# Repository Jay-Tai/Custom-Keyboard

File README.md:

# The Megaboard

The megaboard is a custom 60% keyboard that has 65 keys in total, and has many unique functions that truly make this project a one-of-the-kind.

I built this project to participate in [Hack Club's Stardance](http://stardance.hackclub.com/), and fell in love with the development of keyboards very quickly after I started!
## Features
- Amazing 3D printed case
- 0.91" OLED for animations, startup, and for other tools, such as WPM, and Caps Lock
- SK6812 Mini-E LEDs for under-key glow
- EC11 Rotary Encoder to control volume, scroll through pages, or press down to mute/unmute your zoom meeting
- 65 Akko V3 Cream Yellow Pro keys for your satisfying typing experience needs :D (Cheap and sounds like heaven)
- Topographic look all-around (Part of the PCB is exposed)
w
## CAD Model
All the parts of this project fit together using 2 m2.5 screws.
It has 2 seperate printed pirces, one to be the main base, and the other one to cover the electronics.

Made in OnShape.

## PCB
Here's my PCB! it was made in KiCad. Some footprints and schematics were from marbastlib. I made the silkscreen in Adobe Illustrator.
#### Here is my schematic

#### Here is my PCB

The PCB has 2 copper layers, and all the parts that are needed are part of the PCB design. I think in retrospect, I should have moved the arrow keys to the bottom of the PCB, instead of it being at the top.

## Firmware overview
This hackpad's firmware has been designed in [QMK](https://qmk.fm/). It is a powerful, yet simple way to design keyboards that have a lot of useful functions!
- The rotary encoder controls the volume of the computer, and when you hold FN, you can scroll. When you press the encoder, it will mute/unmute your zoom call.
- The 65 keys all perform different functions that can be adjusted by simply changing it's function in keymap.c.
- The OLED starts off with a startup animation, and then after, it turns into a cat! Specifically, the Bongocat!! <b>Credits to [nwii's bongocat](https://github.com/nwii/oledbongocat) for the source code!</b>
- All keys have SK6812 Mini-E LEDs beneath them and when you press a key, its LED will light up in a reactive typing way. Take a look [here](https://youtu.be/7f3usatOIKM?t=229)!

I might add more in the future, however, that's it for now!

## BOM
Here is everything that you will need to make the megaboard:
Click [here](https://docs.google.com/spreadsheets/d/1aInlIyzgglzUiH9fcOGwBJfbiqagTssbSa5kihXWXrg/edit?usp=sharing)

## Thank you!
Thank you for taking a look! This was a huge undertaking to make this entire project, and I spent over 50 hours to make this!

Especially, thank you to [Hack Club](https://hackclub.com/) for inspiring me to make this project, and thank you to [nwii's bongocat](https://github.com/nwii/oledbongocat) animation for part of the OLED!

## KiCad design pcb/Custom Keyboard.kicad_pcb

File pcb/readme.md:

# PCB Files
The following files are all KiCad files. Download all the files and put them in a folder, and put it in KiCad to edit the PCB!

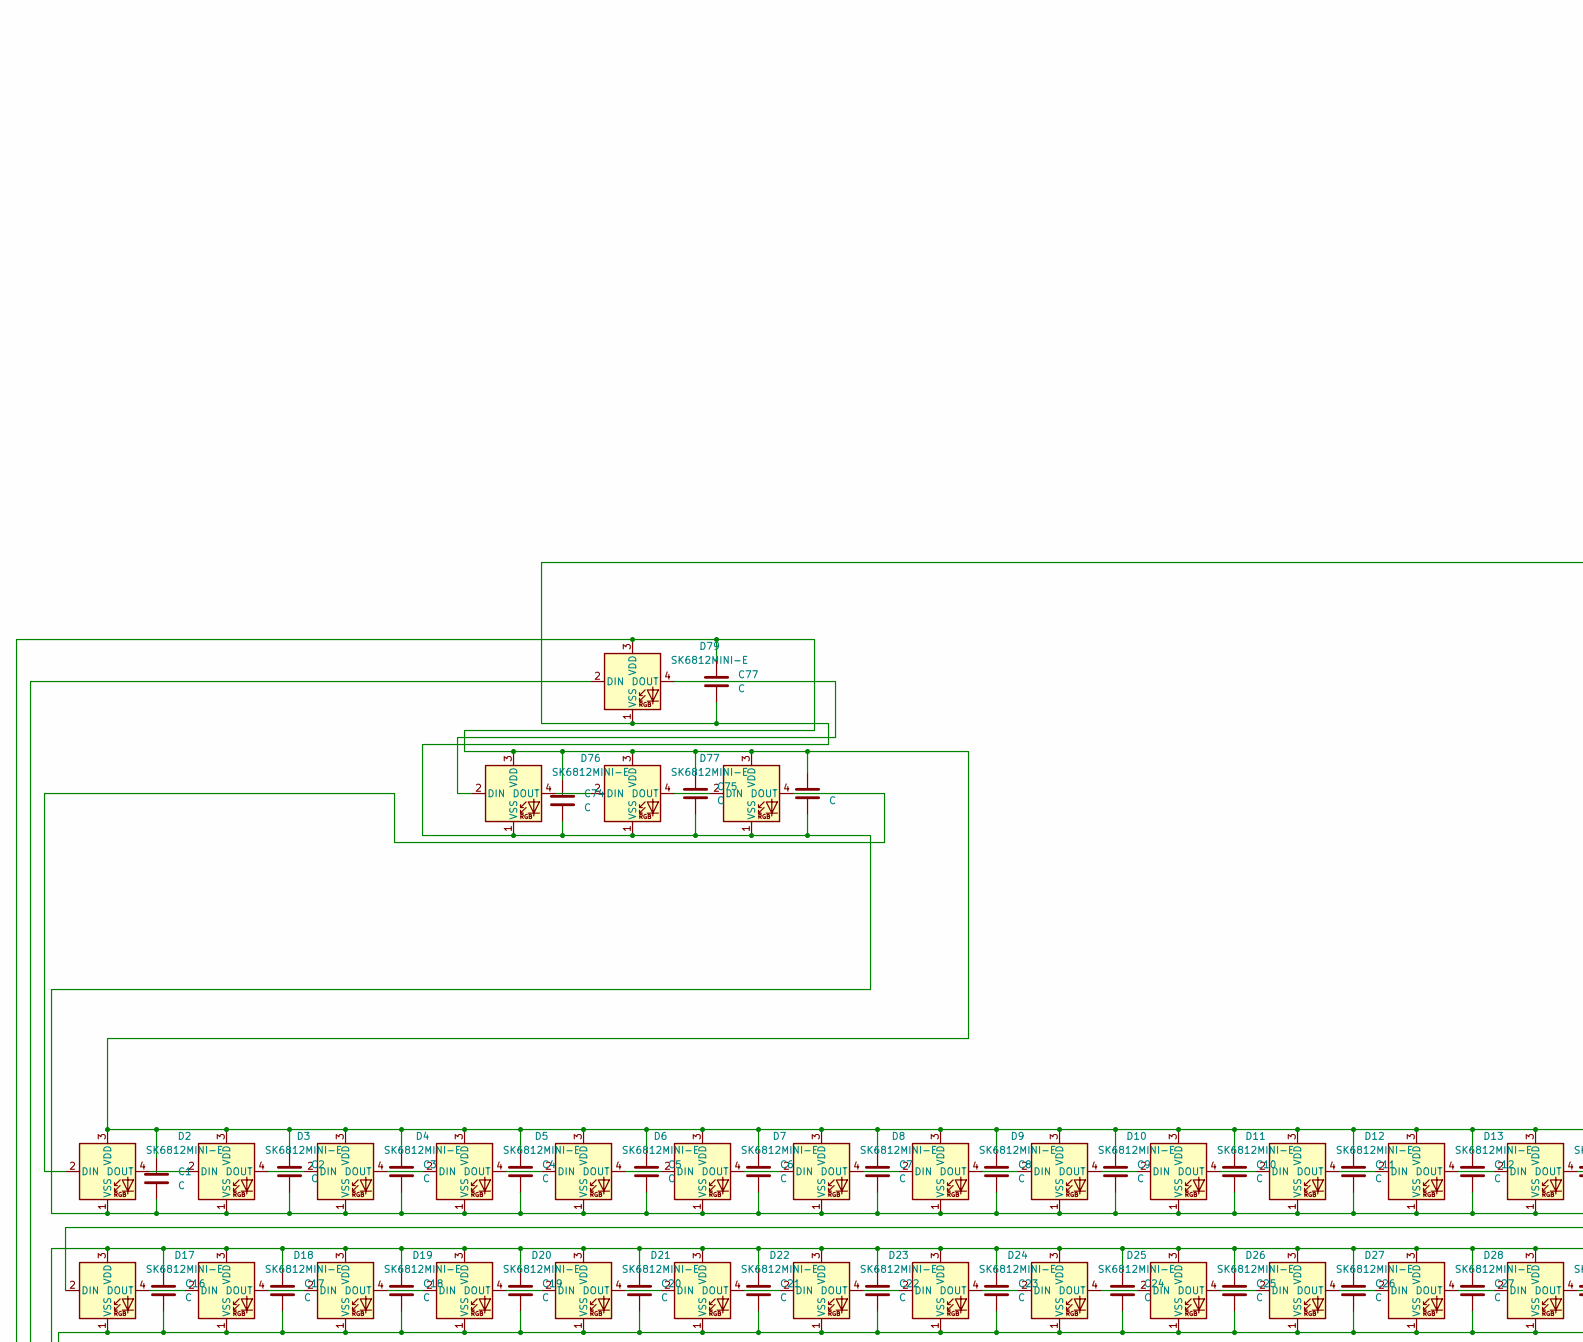
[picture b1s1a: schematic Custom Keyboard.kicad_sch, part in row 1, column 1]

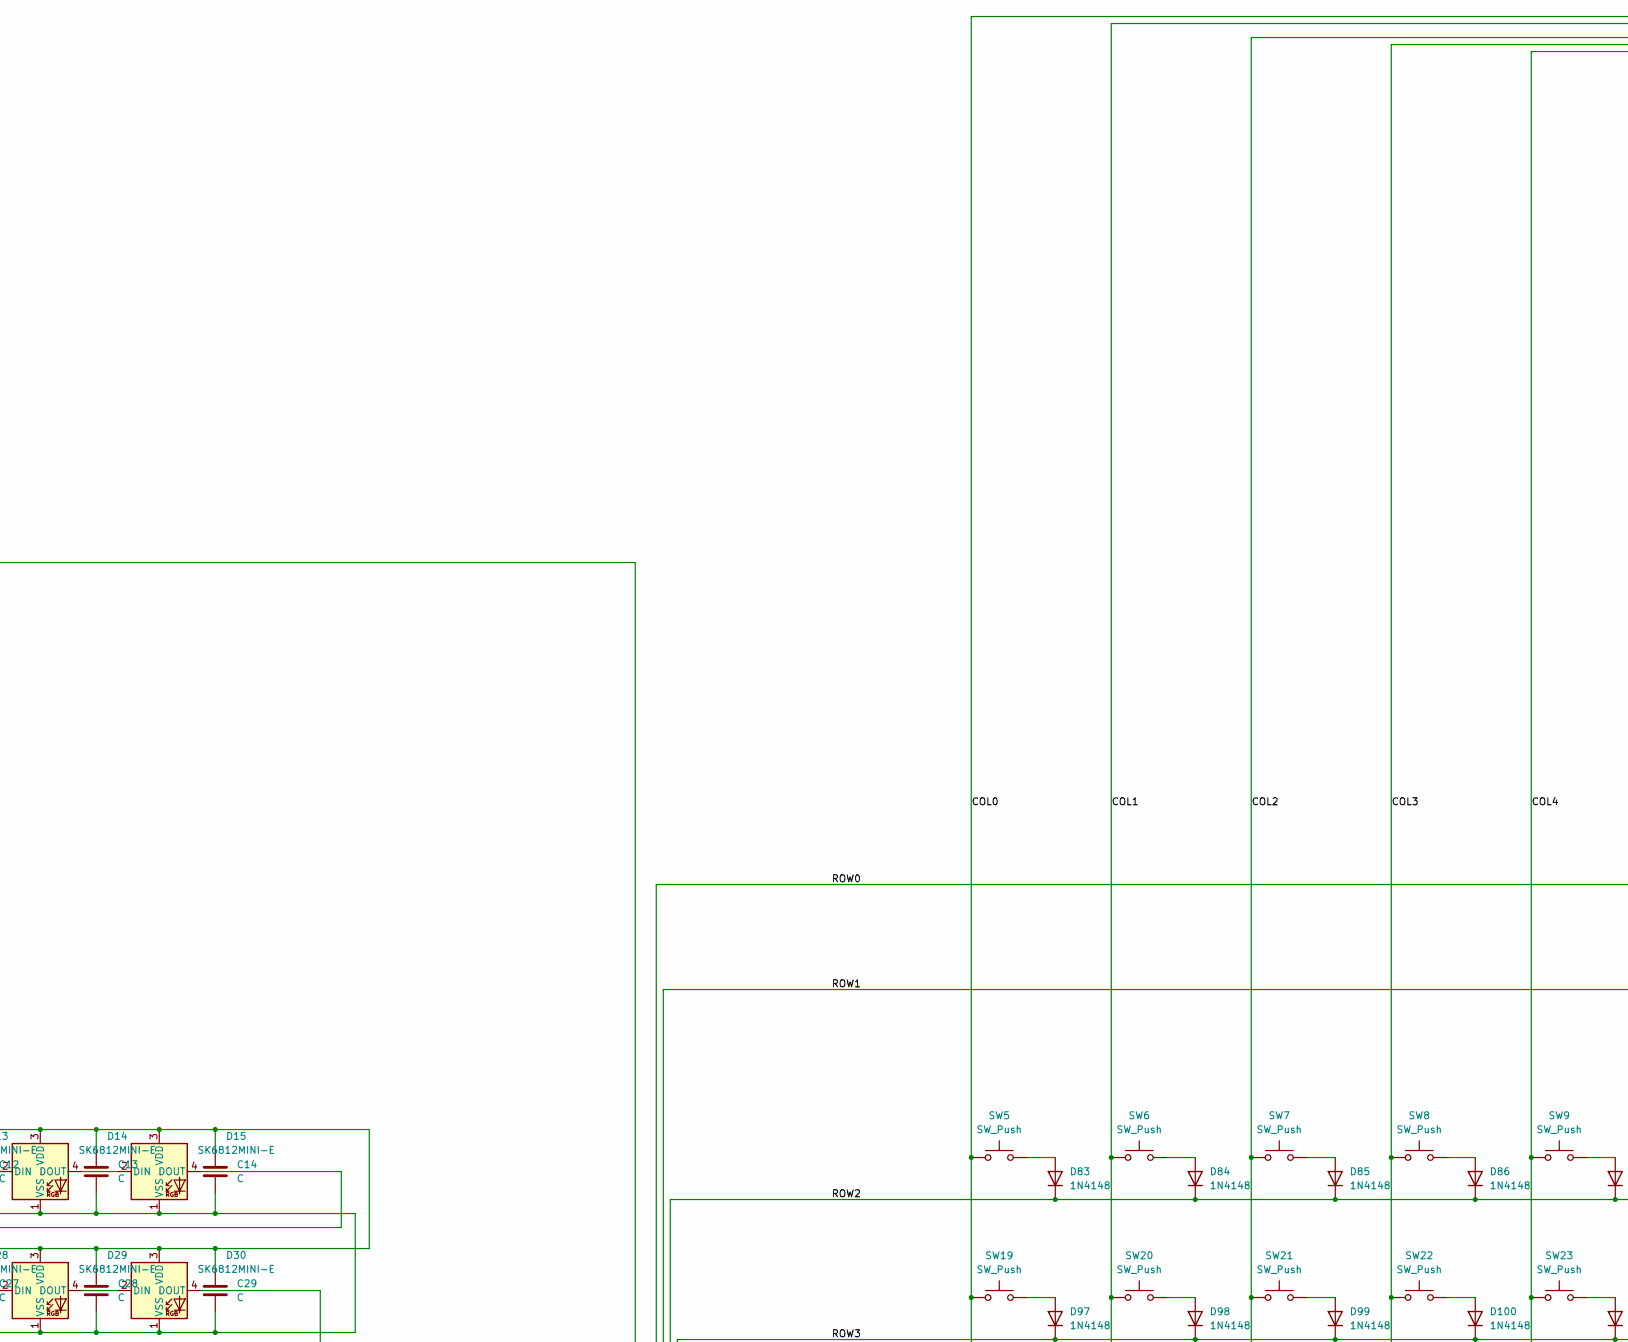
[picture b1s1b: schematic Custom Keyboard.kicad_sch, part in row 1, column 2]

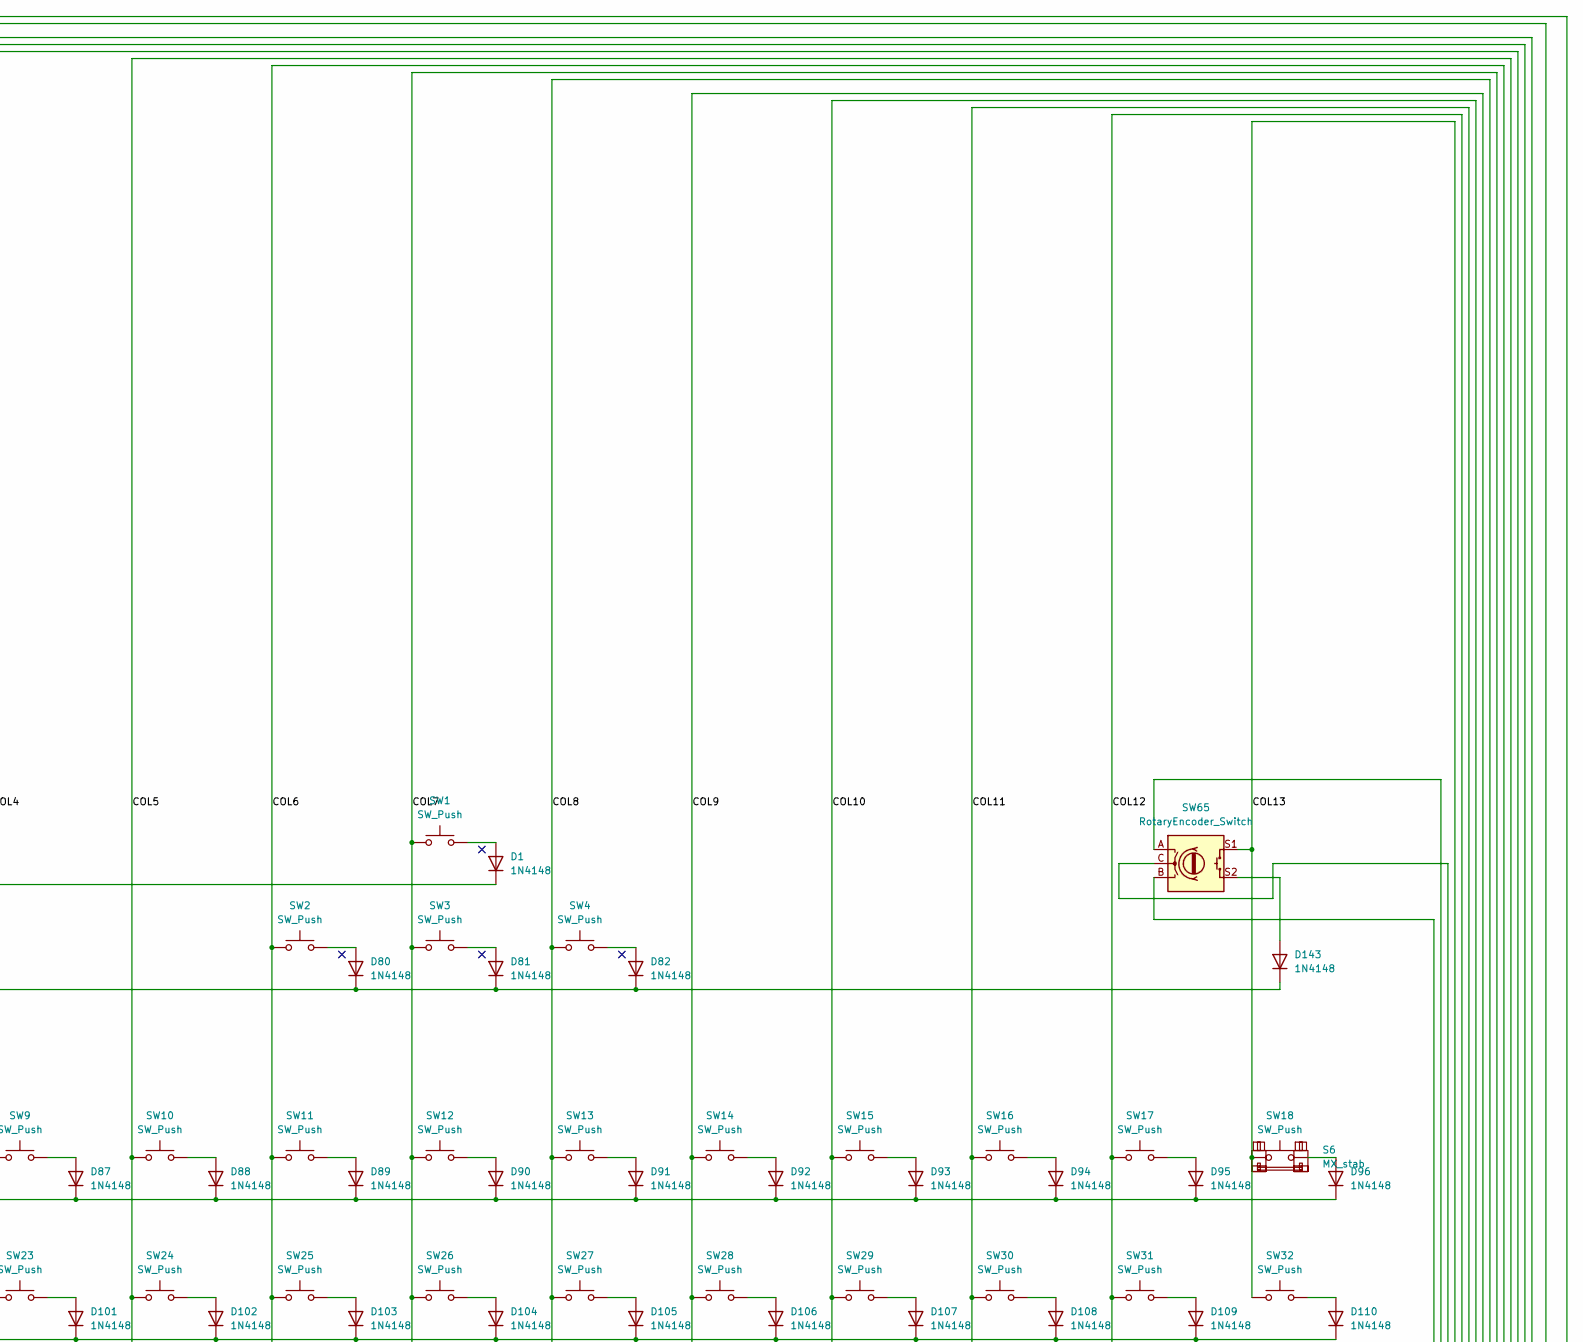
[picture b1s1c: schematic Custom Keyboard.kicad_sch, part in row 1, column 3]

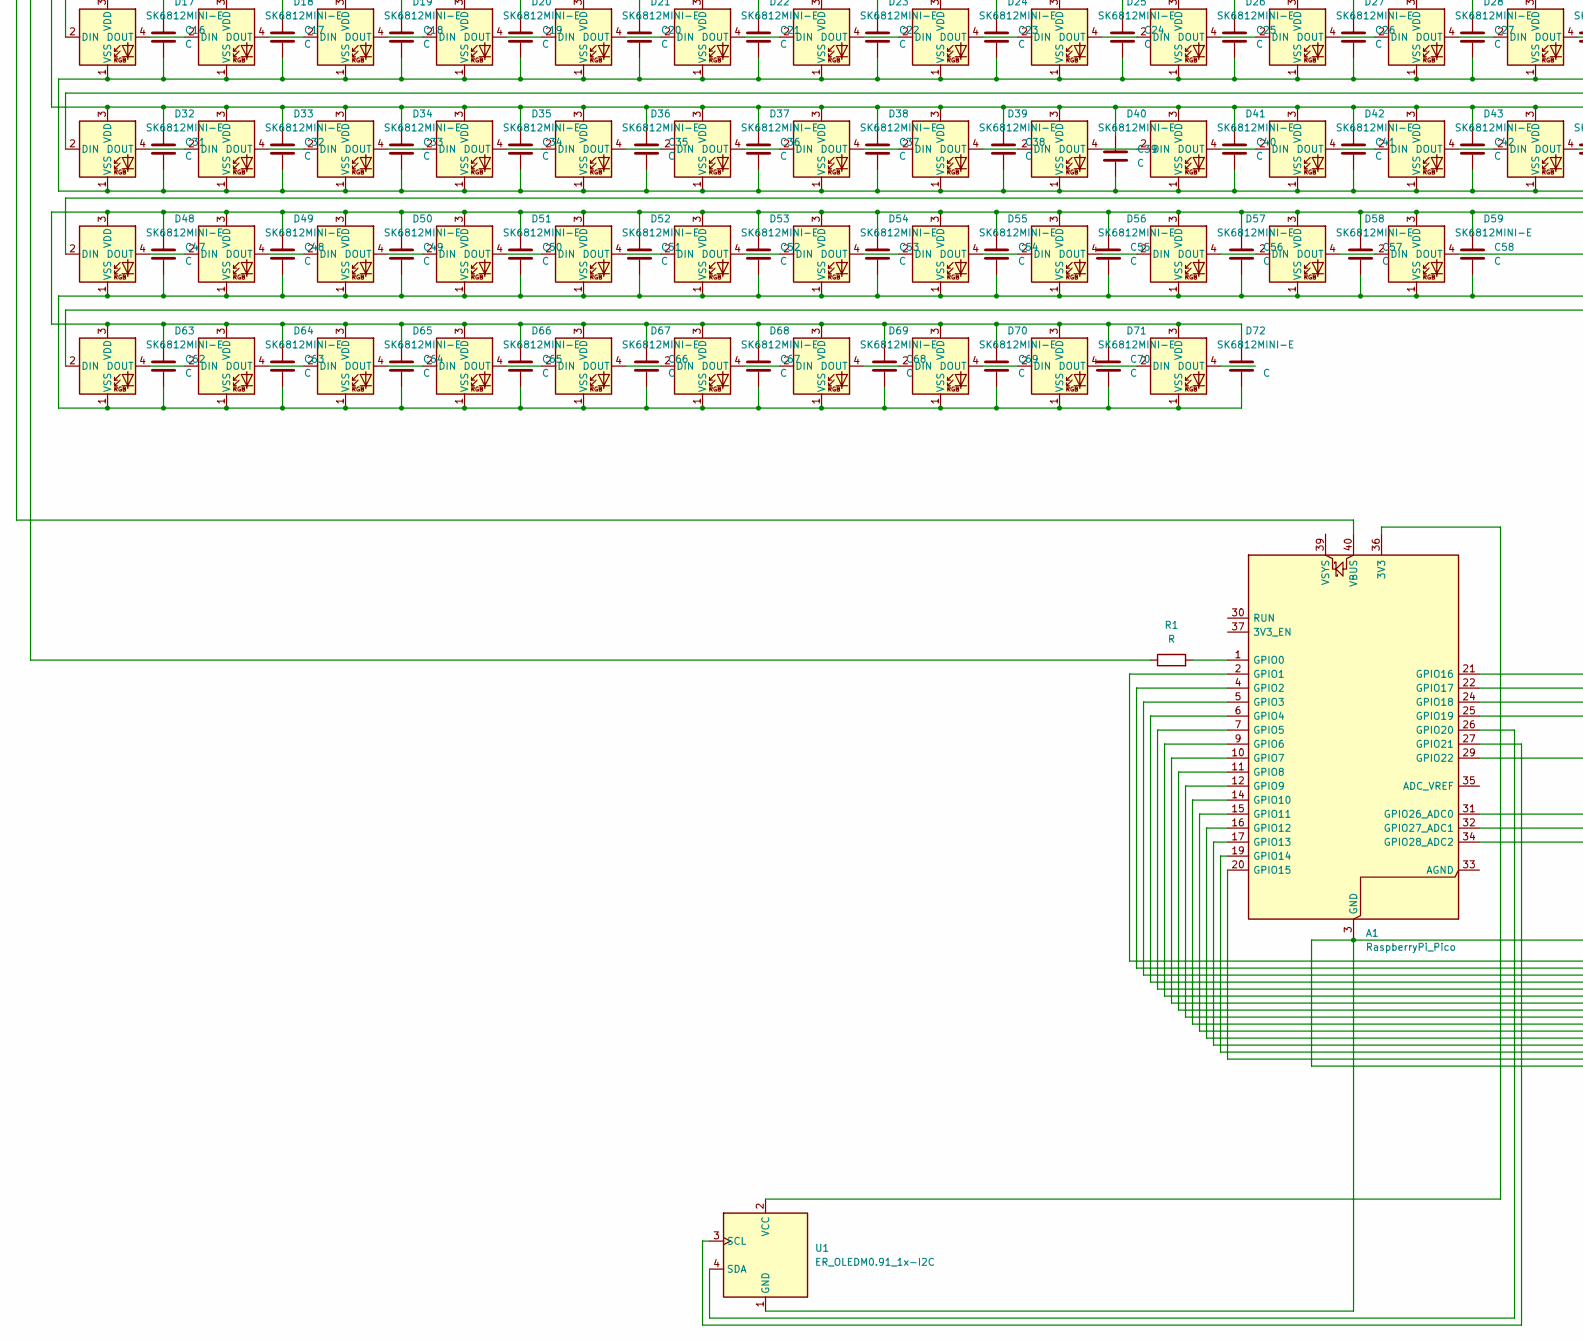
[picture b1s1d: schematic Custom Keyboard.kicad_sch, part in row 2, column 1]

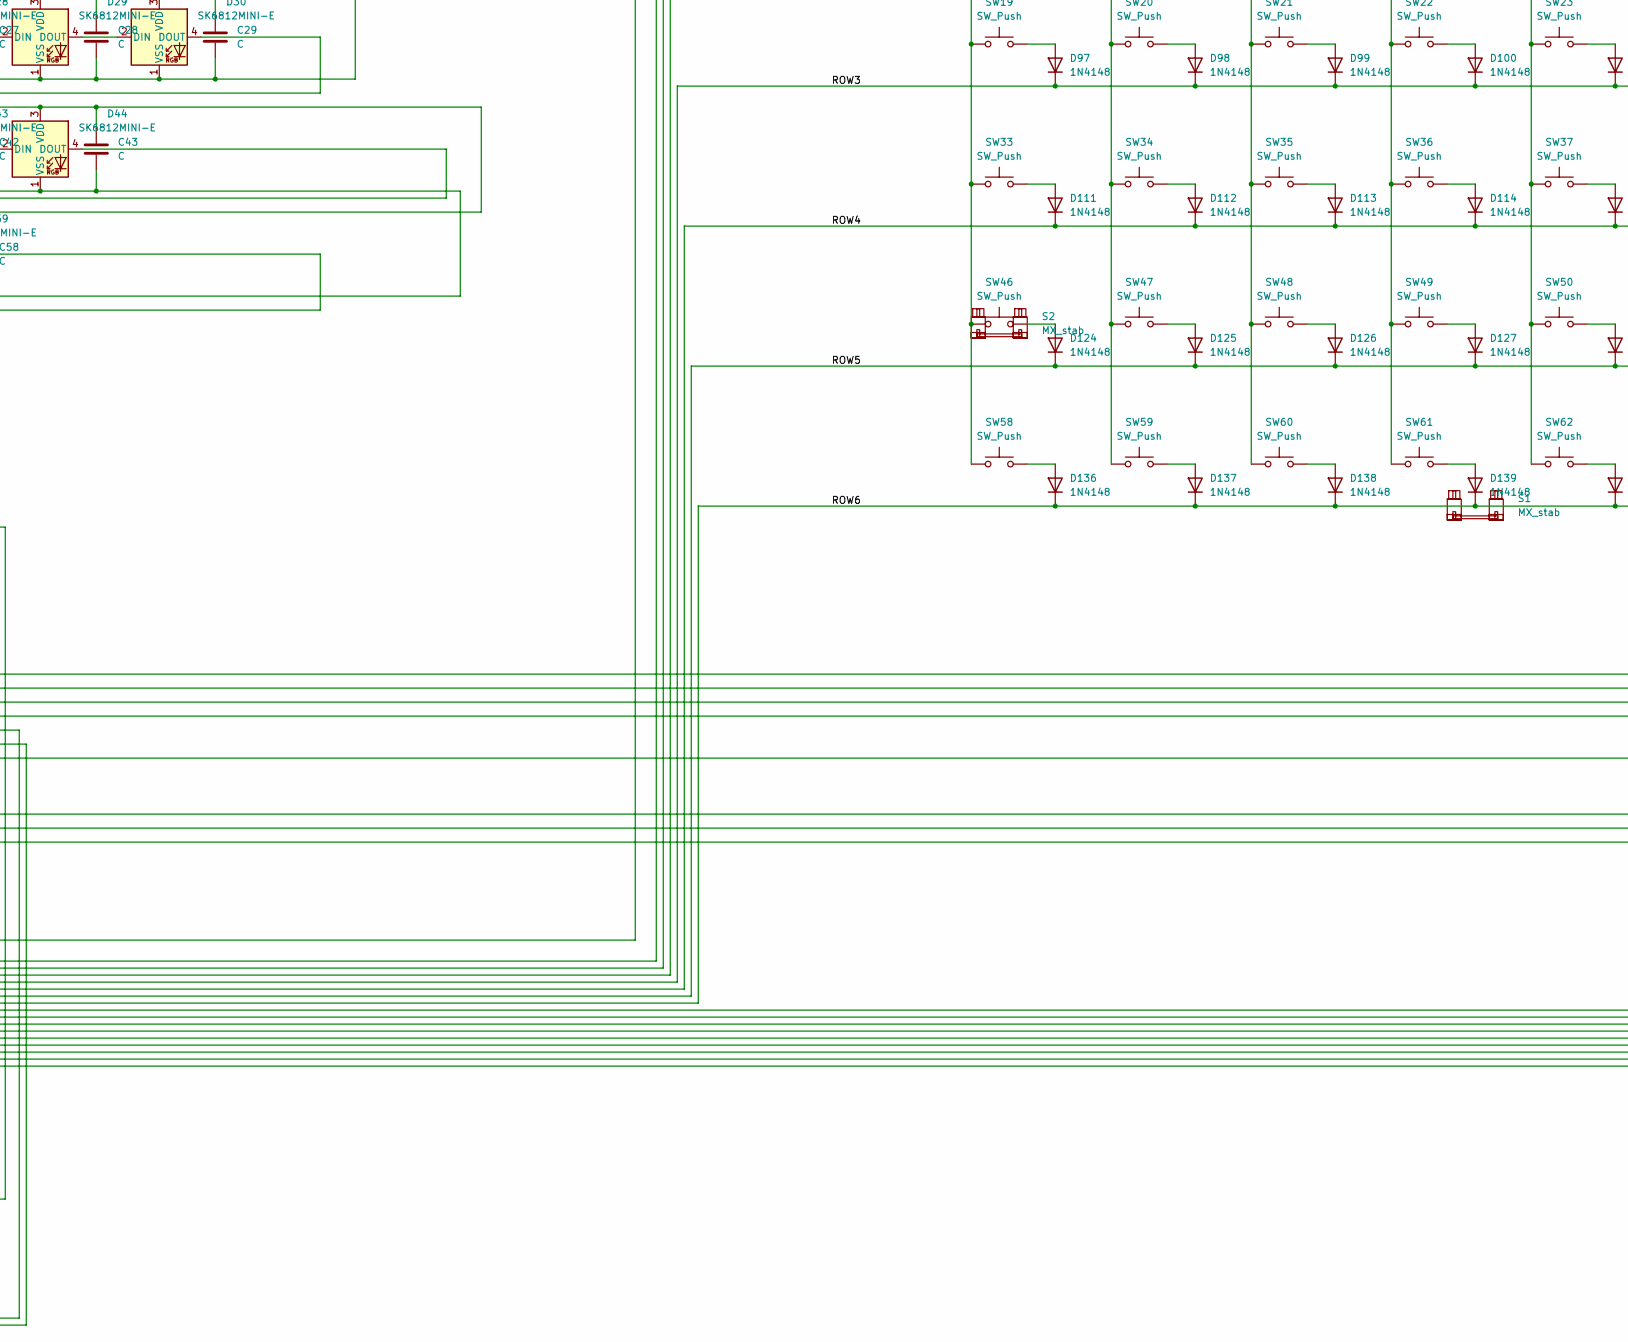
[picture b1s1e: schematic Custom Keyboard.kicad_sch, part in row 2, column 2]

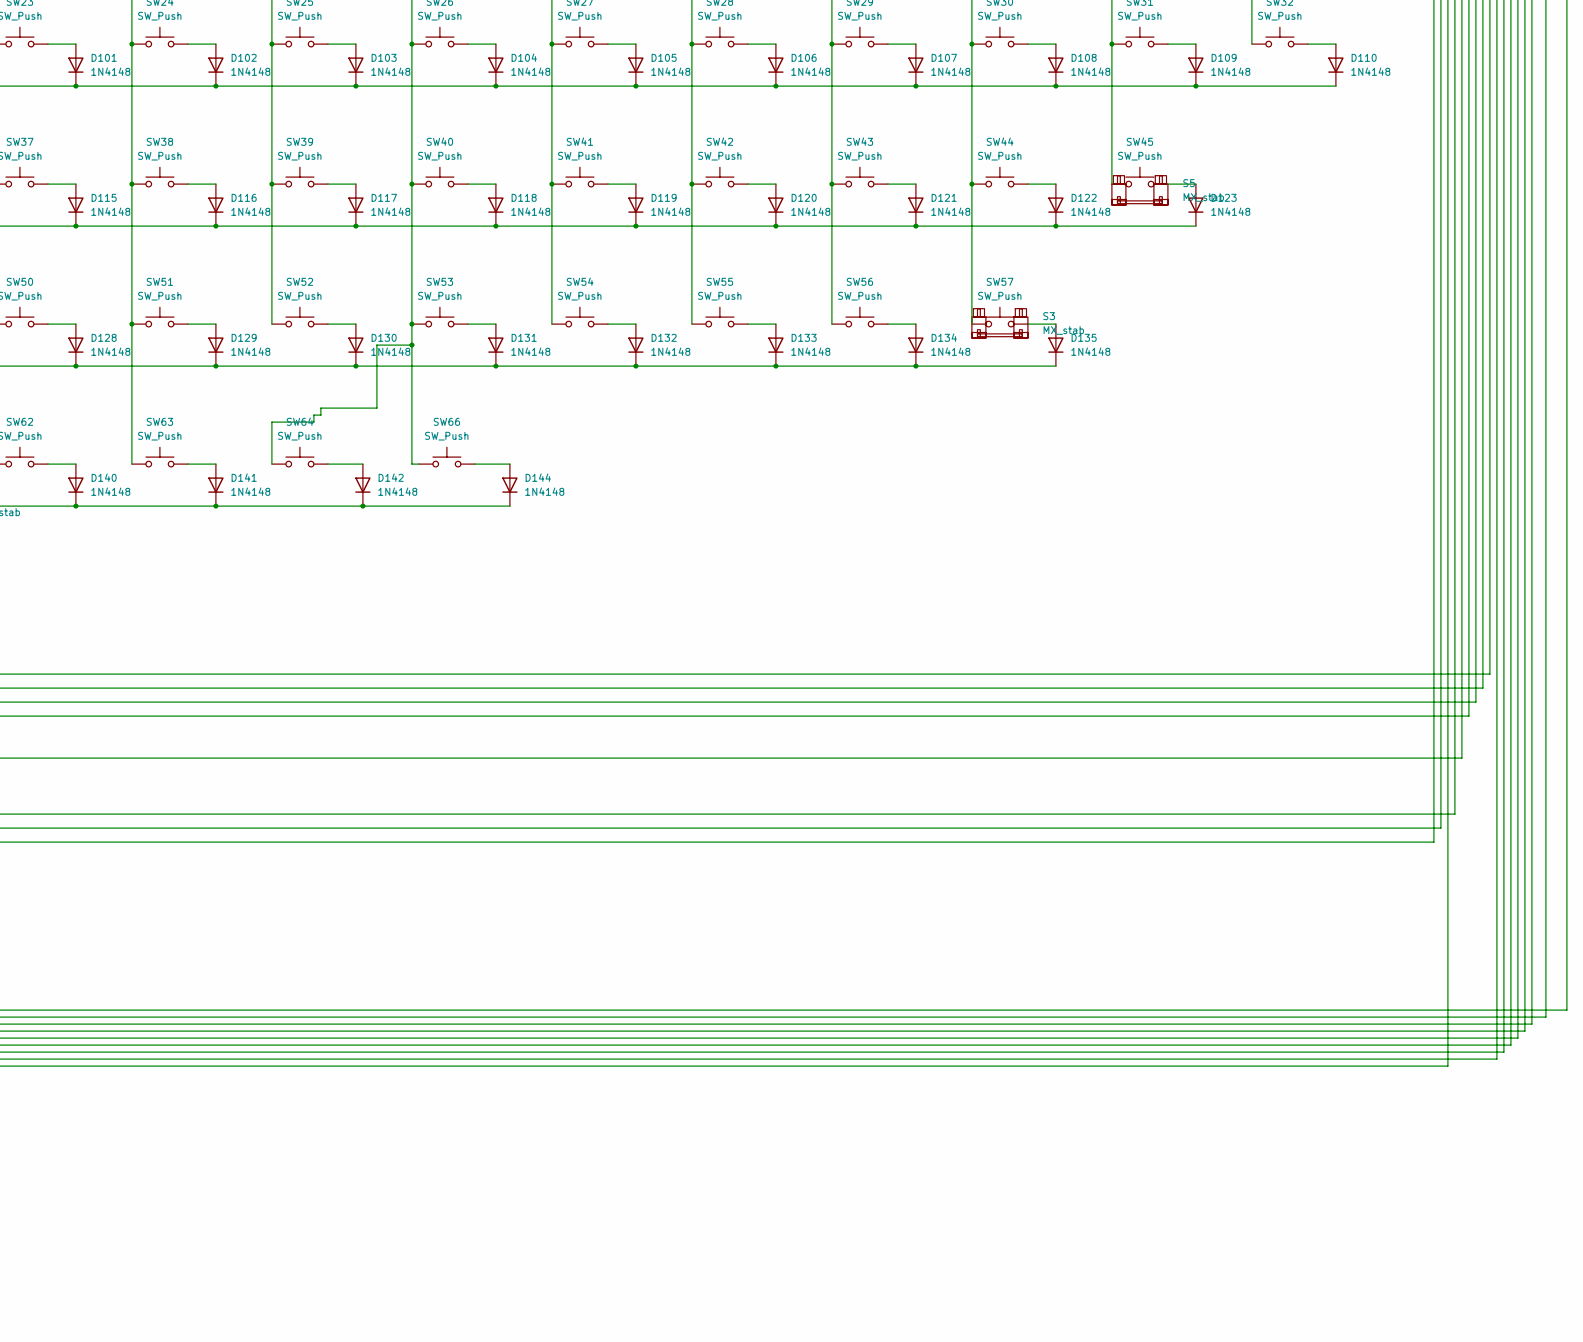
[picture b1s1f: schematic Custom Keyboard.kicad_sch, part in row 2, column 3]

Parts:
A1: RaspberryPi_Pico; RaspberryPi_Pico_Common_THT
C1, C2, C3, C4, C5, C6, C7, C8, C9, C10, C11, C12, C13, C14, C16, C17, C18, C19, C20, C21, C22, C23, C24, C25, C26, C27, C28, C29, C31, C32, C33, C34, C35, C36, C37, C38, C39, C40, C41, C42, C43, C47, C48, C49, C50, C51, C52, C53, C54, C55, C56, C57, C58, C62, C63, C64, C65, C66, C67, C68, C69, C70, C71, C74, C75, C76, C77: C; C_0603_1608Metric_Pad1.08x0.95mm_HandSolder
D1, D80, D81, D82, D83, D84, D85, D86, D87, D88, D89, D90, D91, D92, D93, D94, D95, D96, D97, D98, D99, D100, D101, D102, D103, D104, D105, D106, D107, D108, D109, D110, D111, D112, D113, D114, D115, D116, D117, D118, D119, D120, D121, D122, D123, D124, D125, D126, D127, D128, D129, D130, D131, D132, D133, D134, D135, D136, D137, D138, D139, D140, D141, D142, D143, D144: 1N4148; D_DO-35_SOD27_P7.62mm_Horizontal
D2, D3, D4, D5, D6, D7, D8, D9, D10, D11, D12, D13, D14, D15, D17, D18, D19, D20, D21, D22, D23, D24, D25, D26, D27, D28, D29, D30, D32, D33, D34, D35, D36, D37, D38, D39, D40, D41, D42, D43, D44, D48, D49, D50, D51, D52, D53, D54, D55, D56, D57, D58, D59, D63, D64, D65, D66, D67, D68, D69, D70, D71, D72, D76, D77, D78, D79: SK6812MINI-E; LED_SK6812MINI-E_3.2x2.8mm_P1.5mm_ReverseMount
R1: R; R_0805_2012Metric
S1: MX_stab; STAB_MX_P_6.25u
S2, S5: MX_stab; STAB_MX_2.25u
S3: MX_stab; STAB_MX_P_2.75u
S6: MX_stab; STAB_MX_2u
SW1, SW2, SW3, SW4, SW5, SW6, SW7, SW8, SW9, SW10, SW11, SW12, SW13, SW14, SW15, SW16, SW17, SW18, SW19, SW20, SW21, SW22, SW23, SW24, SW25, SW26, SW27, SW28, SW29, SW30, SW31, SW32, SW33, SW34, SW35, SW36, SW37, SW38, SW39, SW40, SW41, SW42, SW43, SW44, SW45, SW46, SW47, SW48, SW49, SW50, SW51, SW52, SW53, SW54, SW55, SW56, SW57, SW58, SW59, SW60, SW61, SW62, SW63, SW64, SW66: SW_Push; SW_MX_1u
SW65: RotaryEncoder_Switch; RotaryEncoder_Alps_EC11E_Vertical_H20mm
U1: ER_OLEDM0.91_1x-I2C

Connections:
/COL0: A1.11 (GPIO8), SW5.1, SW19.1, SW33.1, SW46.1, SW58.1
/COL1: A1.12 (GPIO9), SW6.1, SW20.1, SW34.1, SW47.1, SW59.1
/COL2: A1.14 (GPIO10), SW7.1, SW21.1, SW35.1, SW48.1, SW60.1
/COL3: A1.15 (GPIO11), SW8.1, SW22.1, SW36.1, SW49.1, SW61.1
/COL4: A1.16 (GPIO12), SW9.1, SW23.1, SW37.1, SW50.1, SW62.1
/COL5: A1.17 (GPIO13), SW10.1, SW24.1, SW38.1, SW51.1, SW63.1
/COL8: A1.21 (GPIO16), SW4.1, SW13.1, SW27.1, SW41.1, SW54.1
/COL9: A1.22 (GPIO17), SW14.1, SW28.1, SW42.1, SW55.1
/COL10: A1.24 (GPIO18), SW15.1, SW29.1, SW43.1, SW56.1
/COL11: A1.25 (GPIO19), SW16.1, SW30.1, SW44.1, SW57.1
/COL12: A1.29 (GPIO22), SW17.1, SW31.1, SW45.1
/COL13: A1.31 (GPIO26_ADC0), SW18.1, SW32.1, SW65.S1
/ROW0: A1.2 (GPIO1), D1.1 (K)
/ROW1: A1.4 (GPIO2), D80.1 (K), D81.1 (K), D82.1 (K), D143.1 (K)
/ROW2: A1.5 (GPIO3), D83.1 (K), D84.1 (K), D85.1 (K), D86.1 (K), D87.1 (K), D88.1 (K), D89.1 (K), D90.1 (K), D91.1 (K), D92.1 (K), D93.1 (K), D94.1 (K), D95.1 (K), D96.1 (K)
/ROW3: A1.6 (GPIO4), D97.1 (K), D98.1 (K), D99.1 (K), D100.1 (K), D101.1 (K), D102.1 (K), D103.1 (K), D104.1 (K), D105.1 (K), D106.1 (K), D107.1 (K), D108.1 (K), D109.1 (K), D110.1 (K)
/ROW4: A1.7 (GPIO5), D111.1 (K), D112.1 (K), D113.1 (K), D114.1 (K), D115.1 (K), D116.1 (K), D117.1 (K), D118.1 (K), D119.1 (K), D120.1 (K), D121.1 (K), D122.1 (K), D123.1 (K)
/ROW5: A1.9 (GPIO6), D124.1 (K), D125.1 (K), D126.1 (K), D127.1 (K), D128.1 (K), D129.1 (K), D130.1 (K), D131.1 (K), D132.1 (K), D133.1 (K), D134.1 (K), D135.1 (K)
/ROW6: A1.10 (GPIO7), D136.1 (K), D137.1 (K), D138.1 (K), D139.1 (K), D140.1 (K), D141.1 (K), D142.1 (K), D144.1 (K)
unnamed: A1.36 (3V3), U1.2 (VCC)
unnamed: A1.1 (GPIO0), R1.2
unnamed: A1.26 (GPIO20), U1.4 (SDA)
unnamed: A1.27 (GPIO21), U1.3 (SCL)
unnamed: A1.32 (GPIO27_ADC1), SW65.A
unnamed: A1.34 (GPIO28_ADC2), SW65.B
unnamed 25: A1.40 (VBUS), C1.1, C2.1, C3.1, C4.1, C5.1, C6.1, C7.1, C8.1, C9.1, C10.1, C11.1, C12.1, C13.1, C14.1, C16.1, C17.1, C18.1, C19.1, C20.1, C21.1, C22.1, C23.1, C24.1, C25.1, C26.1, C27.1, C28.1, C29.1, C31.1, C32.1, C33.1, C34.1, C35.1, C36.1, C37.1, C38.1, C39.1, C40.1, C41.1, C42.1, C43.1, C47.1, C48.1, C49.1, C50.1, C51.1, C52.1, C53.1, C54.1, C55.1, C56.1, C57.1, C58.1, C62.1, C63.1, C64.1, C65.1, C66.1, C67.1, C68.1, C69.1, C70.1, C71.1, C74.1, C75.1, C76.1, C77.1, D2.3 (VDD), D3.3 (VDD), D4.3 (VDD), D5.3 (VDD), D6.3 (VDD), D7.3 (VDD), D8.3 (VDD), D9.3 (VDD), D10.3 (VDD), D11.3 (VDD), D12.3 (VDD), D13.3 (VDD), D14.3 (VDD), D15.3 (VDD), D17.3 (VDD), D18.3 (VDD), D19.3 (VDD), D20.3 (VDD), D21.3 (VDD), D22.3 (VDD), D23.3 (VDD), D24.3 (VDD), D25.3 (VDD), D26.3 (VDD), D27.3 (VDD), D28.3 (VDD), D29.3 (VDD), D30.3 (VDD), D32.3 (VDD), D33.3 (VDD), D34.3 (VDD), D35.3 (VDD), D36.3 (VDD), D37.3 (VDD), D38.3 (VDD), D39.3 (VDD), D40.3 (VDD), D41.3 (VDD), D42.3 (VDD), D43.3 (VDD), D44.3 (VDD), D48.3 (VDD), D49.3 (VDD), D50.3 (VDD), D51.3 (VDD), D52.3 (VDD), D53.3 (VDD), D54.3 (VDD), D55.3 (VDD), D56.3 (VDD), D57.3 (VDD), D58.3 (VDD), D59.3 (VDD), D63.3 (VDD), D64.3 (VDD), D65.3 (VDD), D66.3 (VDD), D67.3 (VDD), D68.3 (VDD), D69.3 (VDD), D70.3 (VDD), D71.3 (VDD), D72.3 (VDD), D76.3 (VDD), D77.3 (VDD), D78.3 (VDD), D79.3 (VDD); also elsewhere on the board
unnamed: D1.2 (A), SW1.2
unnamed: D2.2 (DIN), D78.4 (DOUT)
unnamed: D2.4 (DOUT), D3.2 (DIN)
unnamed: D3.4 (DOUT), D4.2 (DIN)
unnamed: D4.4 (DOUT), D5.2 (DIN)
unnamed: D5.4 (DOUT), D6.2 (DIN)
unnamed: D6.4 (DOUT), D7.2 (DIN)
unnamed: D7.4 (DOUT), D8.2 (DIN)
unnamed: D8.4 (DOUT), D9.2 (DIN)
unnamed: D9.4 (DOUT), D10.2 (DIN)
unnamed: D10.4 (DOUT), D11.2 (DIN)
unnamed 37: A1.3 (GND), A1.8 (GND), A1.13 (GND), A1.18 (GND), A1.23 (GND), A1.28 (GND), A1.38 (GND), C1.2, C2.2, C3.2, C4.2, C5.2, C6.2, C7.2, C8.2, C9.2, C10.2, C11.2, C12.2, C13.2, C14.2, C16.2, C17.2, C18.2, C19.2, C20.2, C21.2, C22.2, C23.2, C24.2, C25.2, C26.2, C27.2, C28.2, C29.2, C31.2, C32.2, C33.2, C34.2, C35.2, C36.2, C37.2, C38.2, C39.2, C40.2, C41.2, C42.2, C43.2, C47.2, C48.2, C49.2, C50.2, C51.2, C52.2, C53.2, C54.2, C55.2, C56.2, C57.2, C58.2, C62.2, C63.2, C64.2, C65.2, C66.2, C67.2, C68.2, C69.2, C70.2, C71.2, C74.2, C75.2, C76.2, C77.2, D2.1 (VSS), D3.1 (VSS), D4.1 (VSS), D5.1 (VSS), D6.1 (VSS), D7.1 (VSS), D8.1 (VSS), D9.1 (VSS), D10.1 (VSS), D11.1 (VSS), D12.1 (VSS), D13.1 (VSS), D14.1 (VSS), D15.1 (VSS), D17.1 (VSS), D18.1 (VSS), D19.1 (VSS), D20.1 (VSS), D21.1 (VSS), D22.1 (VSS), D23.1 (VSS), D24.1 (VSS), D25.1 (VSS), D26.1 (VSS), D27.1 (VSS), D28.1 (VSS), D29.1 (VSS), D30.1 (VSS), D32.1 (VSS), D33.1 (VSS), D34.1 (VSS), D35.1 (VSS), D36.1 (VSS), D37.1 (VSS), D38.1 (VSS), D39.1 (VSS), D40.1 (VSS), D41.1 (VSS), D42.1 (VSS), D43.1 (VSS), D44.1 (VSS), D48.1 (VSS), D49.1 (VSS), D50.1 (VSS), D51.1 (VSS), D52.1 (VSS), D53.1 (VSS), D54.1 (VSS), D55.1 (VSS), D56.1 (VSS), D57.1 (VSS), D58.1 (VSS), D59.1 (VSS), D63.1 (VSS), D64.1 (VSS), D65.1 (VSS), D66.1 (VSS), D67.1 (VSS), D68.1 (VSS), D69.1 (VSS), D70.1 (VSS), D71.1 (VSS), D72.1 (VSS), D76.1 (VSS), D77.1 (VSS), D78.1 (VSS), D79.1 (VSS), SW65.C, U1.1 (GND); also elsewhere on the board
unnamed: D11.4 (DOUT), D12.2 (DIN)
unnamed: D12.4 (DOUT), D13.2 (DIN)
unnamed: D13.4 (DOUT), D14.2 (DIN)
unnamed: D14.4 (DOUT), D15.2 (DIN)
unnamed: D15.4 (DOUT), D17.2 (DIN)
unnamed: D17.4 (DOUT), D18.2 (DIN)
unnamed: D18.4 (DOUT), D19.2 (DIN)
unnamed: D19.4 (DOUT), D20.2 (DIN)
unnamed: D20.4 (DOUT), D21.2 (DIN)
unnamed: D21.4 (DOUT), D22.2 (DIN)
unnamed: D22.4 (DOUT), D23.2 (DIN)
unnamed: D23.4 (DOUT), D24.2 (DIN)
unnamed: D24.4 (DOUT), D25.2 (DIN)
unnamed: D25.4 (DOUT), D26.2 (DIN)
unnamed: D26.4 (DOUT), D27.2 (DIN)
unnamed: D27.4 (DOUT), D28.2 (DIN)
unnamed: D28.4 (DOUT), D29.2 (DIN)
unnamed: D29.4 (DOUT), D30.2 (DIN)
unnamed: D30.4 (DOUT), D32.2 (DIN)
unnamed: D32.4 (DOUT), D33.2 (DIN)
unnamed: D33.4 (DOUT), D34.2 (DIN)
unnamed: D34.4 (DOUT), D35.2 (DIN)
unnamed: D35.4 (DOUT), D36.2 (DIN)
unnamed: D36.4 (DOUT), D37.2 (DIN)
unnamed: D37.4 (DOUT), D38.2 (DIN)
unnamed: D38.4 (DOUT), D39.2 (DIN)
unnamed: D39.4 (DOUT), D40.2 (DIN)
unnamed: D40.4 (DOUT), D41.2 (DIN)
unnamed: D41.4 (DOUT), D42.2 (DIN)
unnamed: D42.4 (DOUT), D43.2 (DIN)
unnamed: D43.4 (DOUT), D44.2 (DIN)
unnamed: D44.4 (DOUT), D48.2 (DIN)
unnamed: D48.4 (DOUT), D49.2 (DIN)
unnamed: D49.4 (DOUT), D50.2 (DIN)
unnamed: D50.4 (DOUT), D51.2 (DIN)
unnamed: D51.4 (DOUT), D52.2 (DIN)
unnamed: D52.4 (DOUT), D53.2 (DIN)
unnamed: D53.4 (DOUT), D54.2 (DIN)
unnamed: D54.4 (DOUT), D55.2 (DIN)
unnamed: D55.4 (DOUT), D56.2 (DIN)
unnamed: D56.4 (DOUT), D57.2 (DIN)
unnamed: D57.4 (DOUT), D58.2 (DIN)
unnamed: D58.4 (DOUT), D59.2 (DIN)
unnamed: D59.4 (DOUT), D63.2 (DIN)
unnamed: D63.4 (DOUT), D64.2 (DIN)
unnamed: D64.4 (DOUT), D65.2 (DIN)
unnamed: D65.4 (DOUT), D66.2 (DIN)
unnamed: D66.4 (DOUT), D67.2 (DIN)
unnamed: D67.4 (DOUT), D68.2 (DIN)
unnamed: D68.4 (DOUT), D69.2 (DIN)
unnamed: D69.4 (DOUT), D70.2 (DIN)
unnamed: D70.4 (DOUT), D71.2 (DIN)
unnamed: D71.4 (DOUT), D72.2 (DIN)
unnamed: D76.2 (DIN), D79.4 (DOUT)
unnamed: D76.4 (DOUT), D77.2 (DIN)
unnamed: D77.4 (DOUT), D78.2 (DIN)
unnamed: D79.2 (DIN), R1.1
unnamed: D80.2 (A), SW2.2
unnamed: D81.2 (A), SW3.2
unnamed: D82.2 (A), SW4.2
unnamed: D83.2 (A), SW5.2
unnamed: D84.2 (A), SW6.2
unnamed: D85.2 (A), SW7.2
unnamed: D86.2 (A), SW8.2
unnamed: D87.2 (A), SW9.2
unnamed: D88.2 (A), SW10.2
unnamed: D89.2 (A), SW11.2
unnamed: D90.2 (A), SW12.2
unnamed: D91.2 (A), SW13.2
unnamed: D92.2 (A), SW14.2
unnamed: D93.2 (A), SW15.2
unnamed: D94.2 (A), SW16.2
unnamed: D95.2 (A), SW17.2
unnamed: D96.2 (A), SW18.2
unnamed: D97.2 (A), SW19.2
unnamed: D98.2 (A), SW20.2
unnamed: D99.2 (A), SW21.2
unnamed: D100.2 (A), SW22.2
unnamed: D101.2 (A), SW23.2
unnamed: D102.2 (A), SW24.2
unnamed: D103.2 (A), SW25.2
unnamed: D104.2 (A), SW26.2
unnamed: D105.2 (A), SW27.2
unnamed: D106.2 (A), SW28.2
unnamed: D107.2 (A), SW29.2
unnamed: D108.2 (A), SW30.2
unnamed: D109.2 (A), SW31.2
unnamed: D110.2 (A), SW32.2
unnamed: D111.2 (A), SW33.2
unnamed: D112.2 (A), SW34.2
unnamed: D113.2 (A), SW35.2
unnamed: D114.2 (A), SW36.2
unnamed: D115.2 (A), SW37.2
unnamed: D116.2 (A), SW38.2
unnamed: D117.2 (A), SW39.2
unnamed: D118.2 (A), SW40.2
unnamed: D119.2 (A), SW41.2
unnamed: D120.2 (A), SW42.2
unnamed: D121.2 (A), SW43.2
unnamed: D122.2 (A), SW44.2
unnamed: D123.2 (A), SW45.2
unnamed: D124.2 (A), SW46.2
unnamed: D125.2 (A), SW47.2
unnamed: D126.2 (A), SW48.2
unnamed: D127.2 (A), SW49.2
unnamed: D128.2 (A), SW50.2
unnamed: D129.2 (A), SW51.2
unnamed: D130.2 (A), SW52.2
unnamed: D131.2 (A), SW53.2
unnamed: D132.2 (A), SW54.2
unnamed: D133.2 (A), SW55.2
unnamed: D134.2 (A), SW56.2
unnamed: D135.2 (A), SW57.2
unnamed: D136.2 (A), SW58.2
unnamed: D137.2 (A), SW59.2
unnamed: D138.2 (A), SW60.2
unnamed: D139.2 (A), SW61.2
unnamed: D140.2 (A), SW62.2
unnamed: D141.2 (A), SW63.2
unnamed: D142.2 (A), SW64.2
unnamed: D143.2 (A), SW65.S2
unnamed: D144.2 (A), SW66.2

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
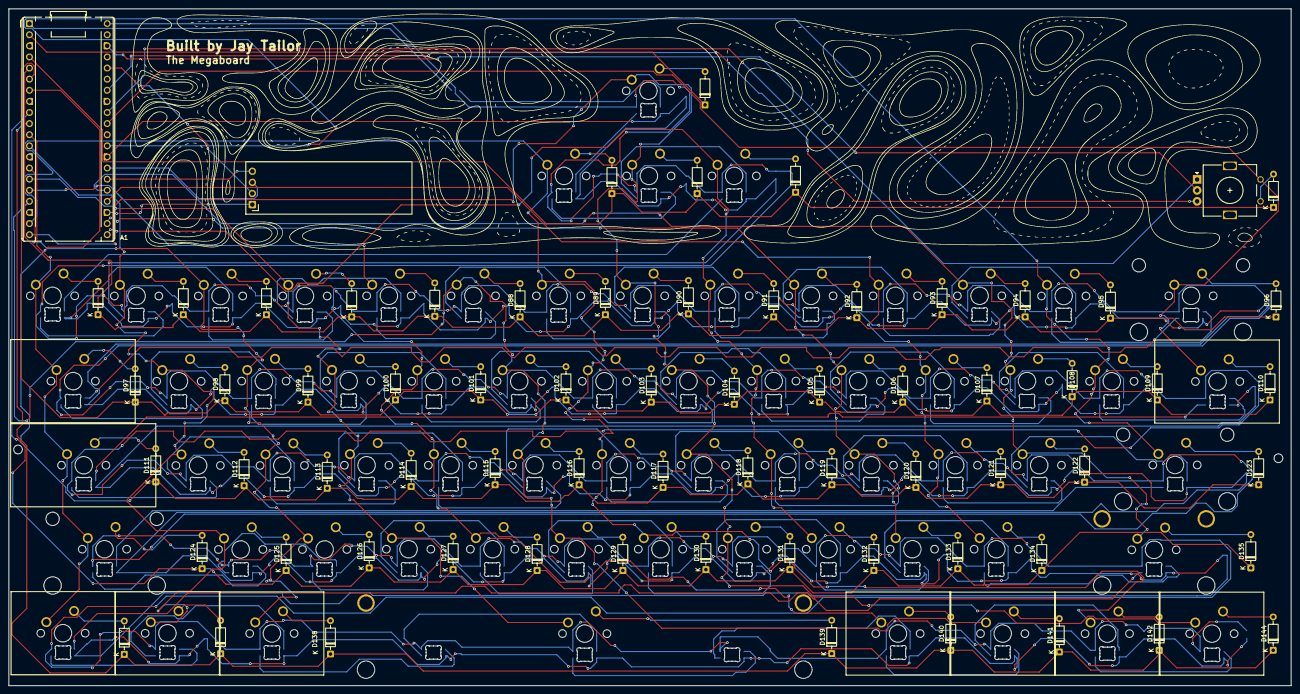
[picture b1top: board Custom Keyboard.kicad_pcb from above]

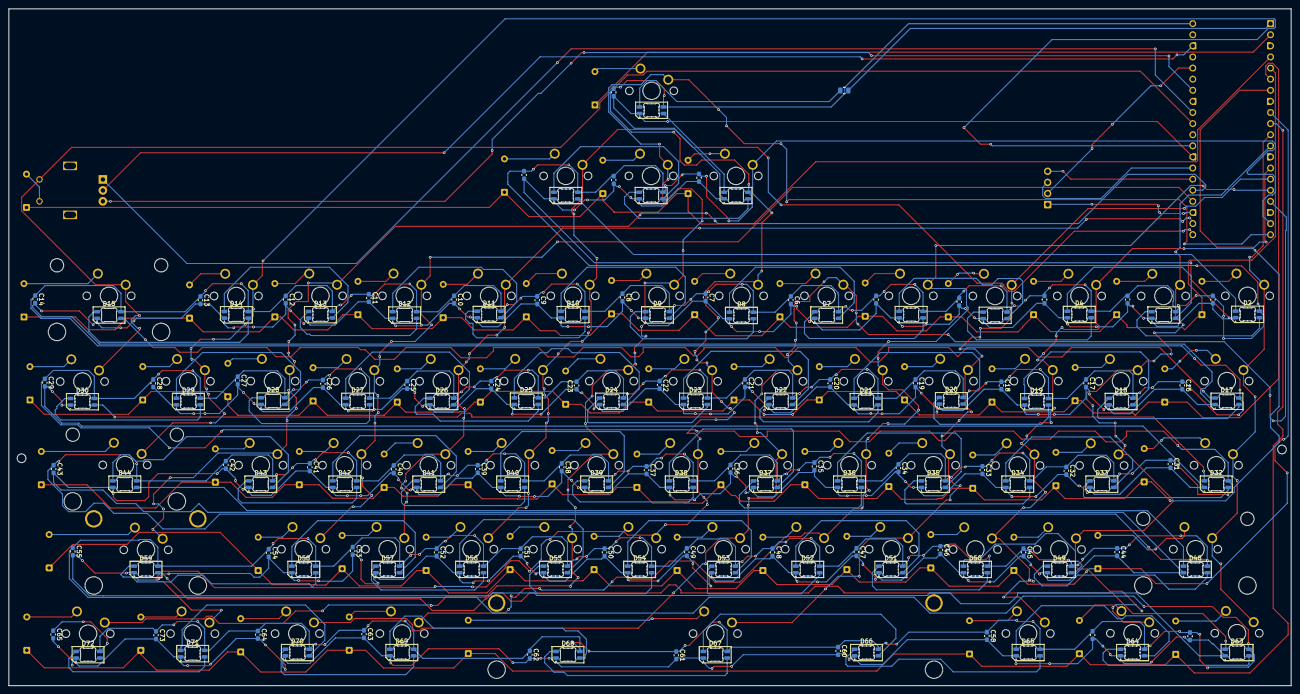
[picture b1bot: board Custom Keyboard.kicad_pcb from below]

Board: 2 copper layers, 293.2 x 154.8 mm, 274 parts (135 on the bottom side), 162 nets.

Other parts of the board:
C44, C45, C46, C60, C61, C73: C; C_0603_1608Metric_Pad1.08x0.95mm_HandSolder

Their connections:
unnamed 25: C44.1, C45.1, C46.1, C60.1, C61.1, C73.1; also elsewhere on the board
unnamed 37: C44.2, C45.2, C46.2, C60.2, C61.2, C73.2; also elsewhere on the board
